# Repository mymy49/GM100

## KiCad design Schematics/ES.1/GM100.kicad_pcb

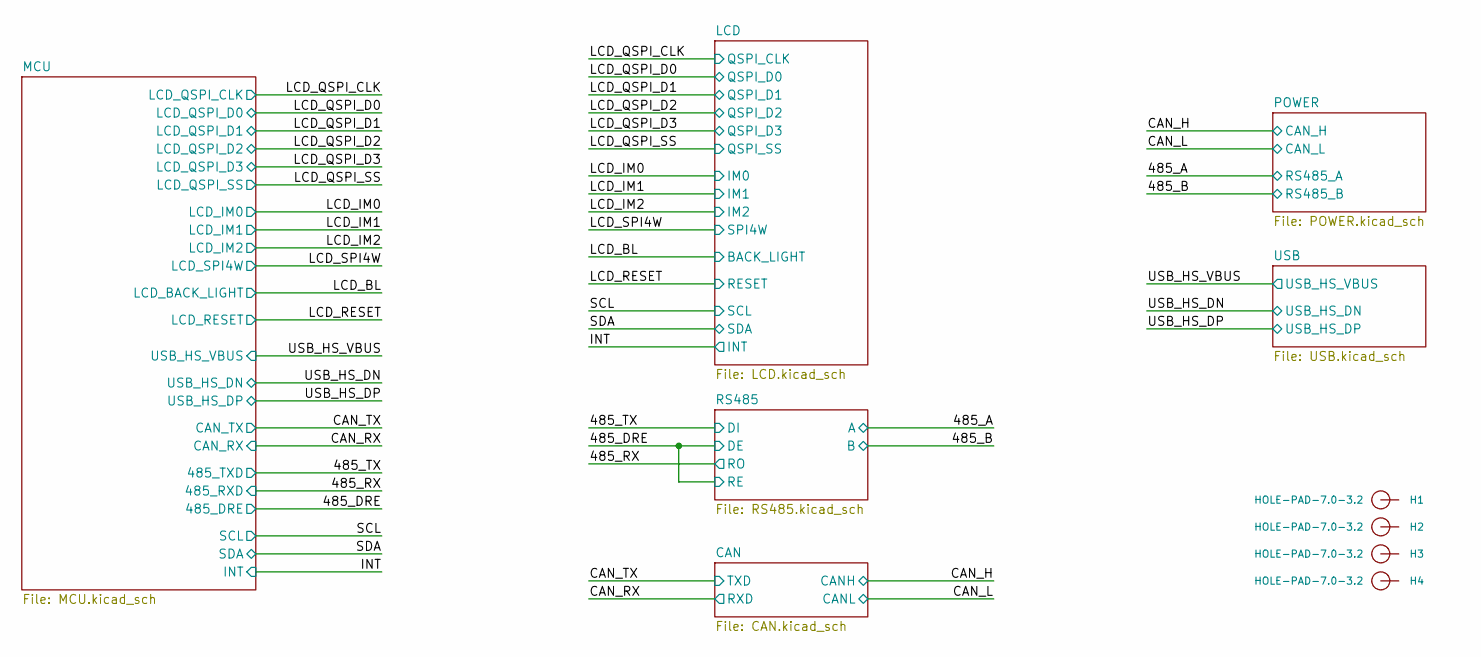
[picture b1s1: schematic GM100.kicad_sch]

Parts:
H1, H2, H3, H4: HOLE-PAD-7.0-3.2; Hole_7_0_3_2

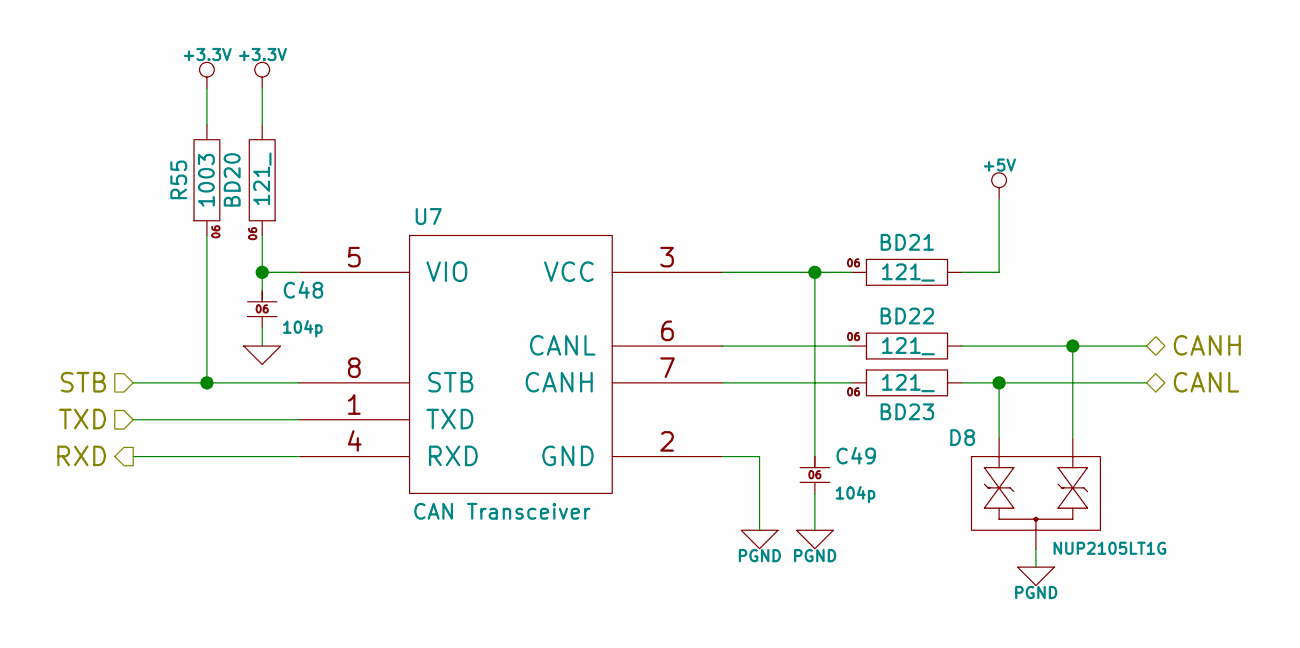
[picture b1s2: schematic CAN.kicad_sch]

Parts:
BD20, BD21, BD22, BD23: BLM18KG121TN1D; 0603; LCSC Part # C85831
C48, C49: 0603B104K500; 0603; LCSC Part # C314282
D8: NUP2105LT1G; SOT23; LCSC Part # C14486
R55: WR06X1003FTL; 0603; LCSC Part # C132374
U7: CA-IF1042LVS-Q1; SOIC-8; LCSC Part # C20598902

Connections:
+3.3V: BD20.2, R55.2; also elsewhere on the board
+5V: BD21.2; also elsewhere on the board
/CAN/STB: R55.1, U7.8 (STB)
/CAN_H: BD22.2, D8.2 (C1); also elsewhere on the board
/CAN_L: BD23.2, D8.1 (A2); also elsewhere on the board
/CAN_RX: U7.4 (RXD); also elsewhere on the board
/CAN_TX: U7.1 (TXD); also elsewhere on the board
GND: C48.1; also elsewhere on the board
unnamed: BD23.1, U7.7 (CANH)
unnamed: BD22.1, U7.6 (CANL)
unnamed: BD21.1, C49.2, U7.3 (VCC)
unnamed: BD20.1, C48.2, U7.5 (VIO)
PGND: C49.1, D8.3 (A1C2), U7.2 (GND); also elsewhere on the board

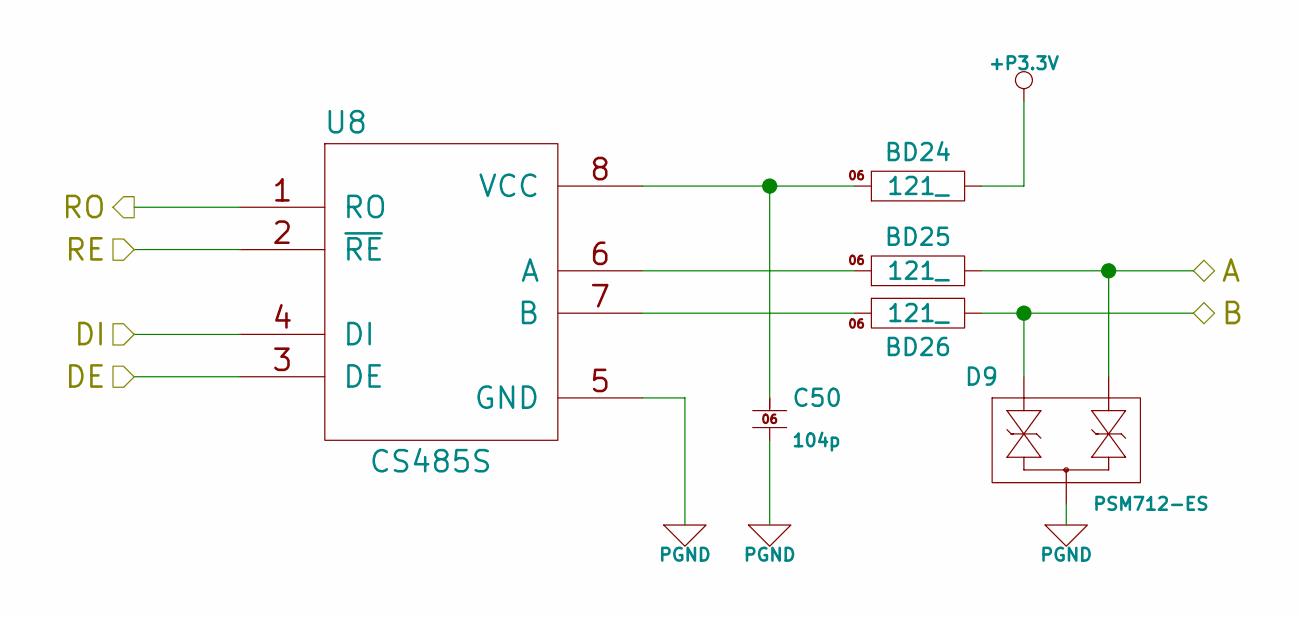
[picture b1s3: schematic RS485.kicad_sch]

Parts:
BD24, BD25, BD26: BLM18KG121TN1D; 0603; LCSC Part # C85831
C50: 0603B104K500; 0603; LCSC Part # C314282
D9: PSM712-ES; SOT23; LCSC Part # C5180294
U8: CS485S; SOIC-8; LCSC Part # C7422593

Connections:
+P3.3V: BD24.2; also elsewhere on the board
/485_A: BD25.2, D9.2 (C1); also elsewhere on the board
/485_B: BD26.2, D9.1 (A2); also elsewhere on the board
/485_DRE: U8.2 (~RE), U8.3 (DE); also elsewhere on the board
/485_RX: U8.1 (RO); also elsewhere on the board
/485_TX: U8.4 (DI); also elsewhere on the board
unnamed: BD25.1, U8.6 (A)
unnamed: BD26.1, U8.7 (B)
unnamed: BD24.1, C50.2, U8.8 (VCC)
PGND: C50.1, D9.3 (A1C2), U8.5 (GND); also elsewhere on the board

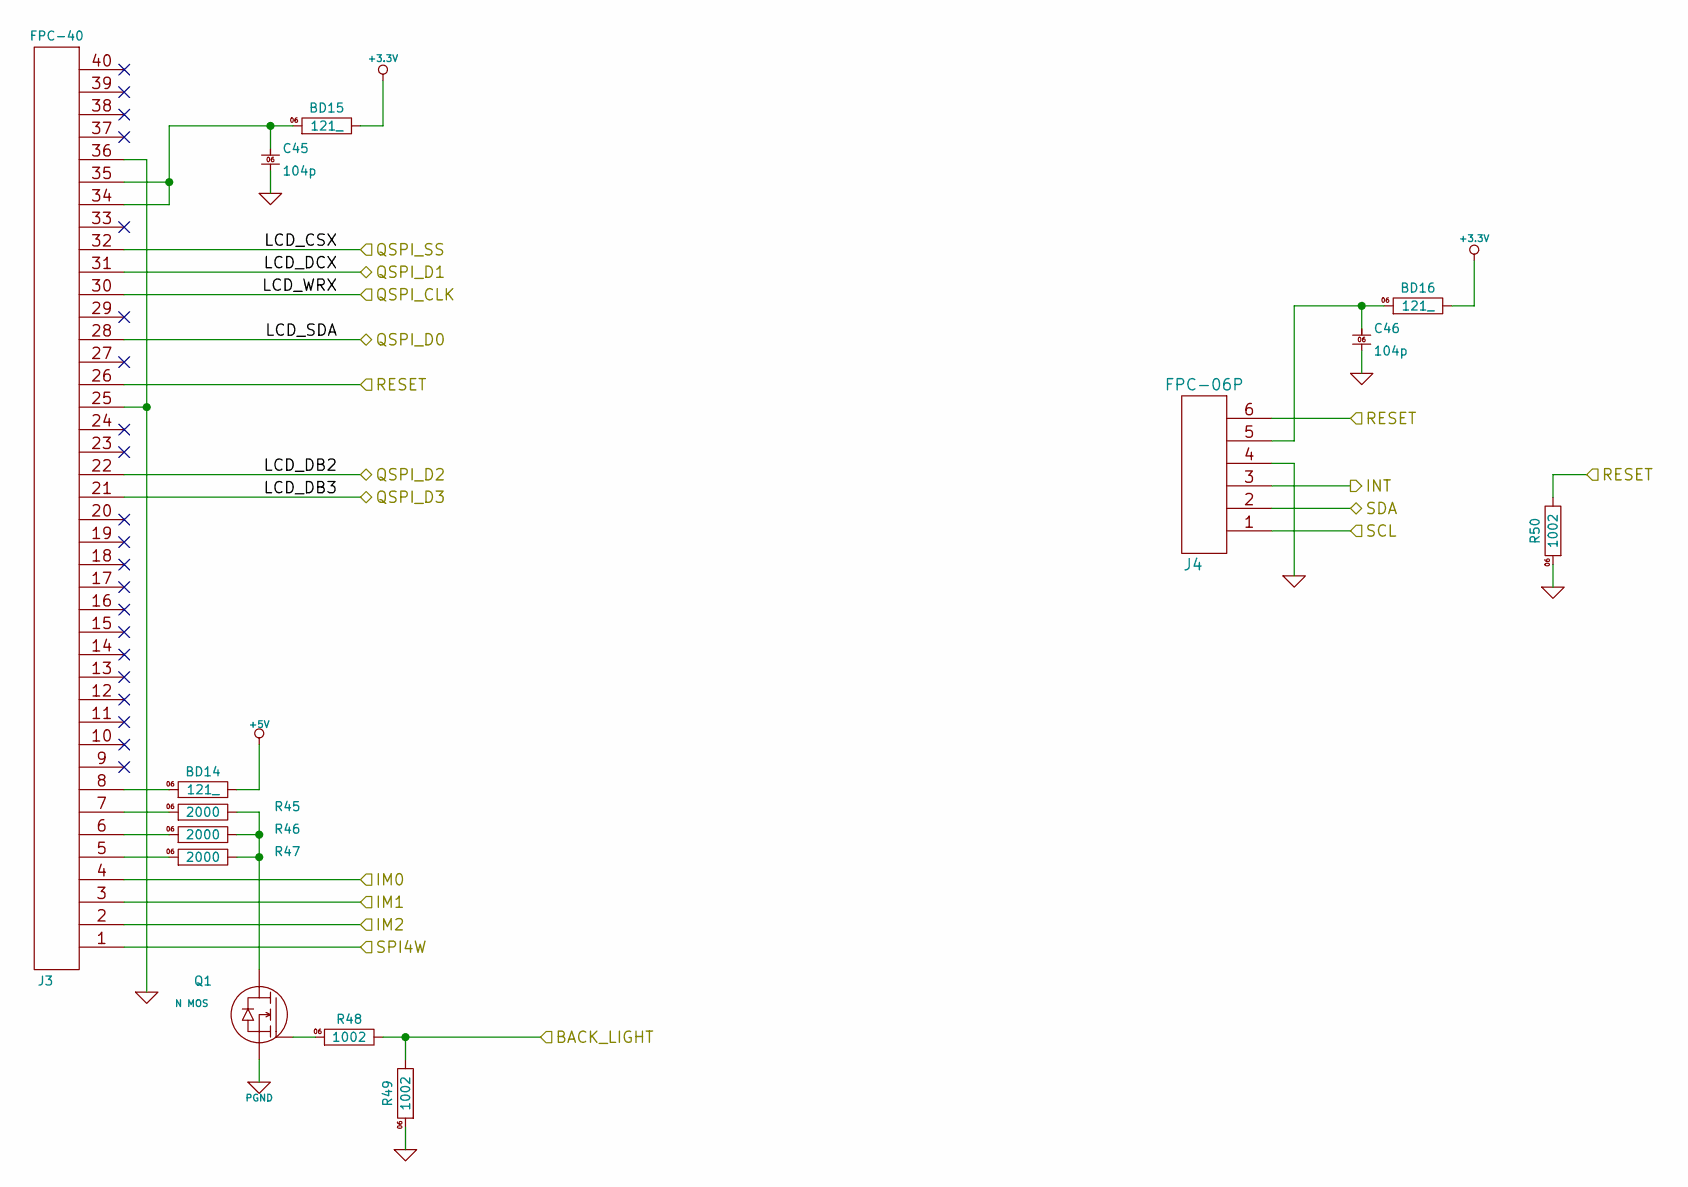
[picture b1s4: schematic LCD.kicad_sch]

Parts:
BD14, BD15, BD16: BLM18KG121TN1D; 0603; LCSC Part # C85831
C45, C46: 0603B104K500; 0603; LCSC Part # C314282
J3: AFC24-S40FIA-00; JUSHUO_AFC24-S40FIA-00; LCSC Part # C262686
J4: AFC24-S06FIA-00; JUSHUO_AFC24-S06FIA-00; LCSC Part # C262679
Q1: 2N7002K-7; SOT23; LCSC Part # C85047
R45, R46, R47: WR06X2000FTL; 0603; LCSC Part # C163878
R48, R49, R50: WR06X1002FTL; 0603; LCSC Part # C108449

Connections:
+3.3V: BD15.2, BD16.2; also elsewhere on the board
+5V: BD14.2; also elsewhere on the board
/INT: J4.3; also elsewhere on the board
/LCD_BL: R48.2, R49.2; also elsewhere on the board
/LCD_IM0: J3.4; also elsewhere on the board
/LCD_IM1: J3.3; also elsewhere on the board
/LCD_IM2: J3.2; also elsewhere on the board
/LCD_QSPI_CLK: J3.30; also elsewhere on the board
/LCD_QSPI_D0: J3.28; also elsewhere on the board
/LCD_QSPI_D1: J3.31; also elsewhere on the board
/LCD_QSPI_D2: J3.22; also elsewhere on the board
/LCD_QSPI_D3: J3.21; also elsewhere on the board
/LCD_QSPI_SS: J3.32; also elsewhere on the board
/LCD_RESET: J3.26, J4.6, R50.2; also elsewhere on the board
/LCD_SPI4W: J3.1; also elsewhere on the board
/SCL: J4.1; also elsewhere on the board
/SDA: J4.2; also elsewhere on the board
GND: C45.1, C46.1, J3.25, J3.36, J4.4, R49.1, R50.1; also elsewhere on the board
unnamed: BD14.1, J3.8
unnamed: BD15.1, C45.2, J3.34, J3.35
unnamed: BD16.1, C46.2, J4.5
unnamed: J3.5, R47.1
unnamed: J3.6, R46.1
unnamed: J3.7, R45.1
unnamed: Q1.3 (D), R45.2, R46.2, R47.2
unnamed: Q1.1 (G), R48.1
PGND: Q1.2 (S); also elsewhere on the board

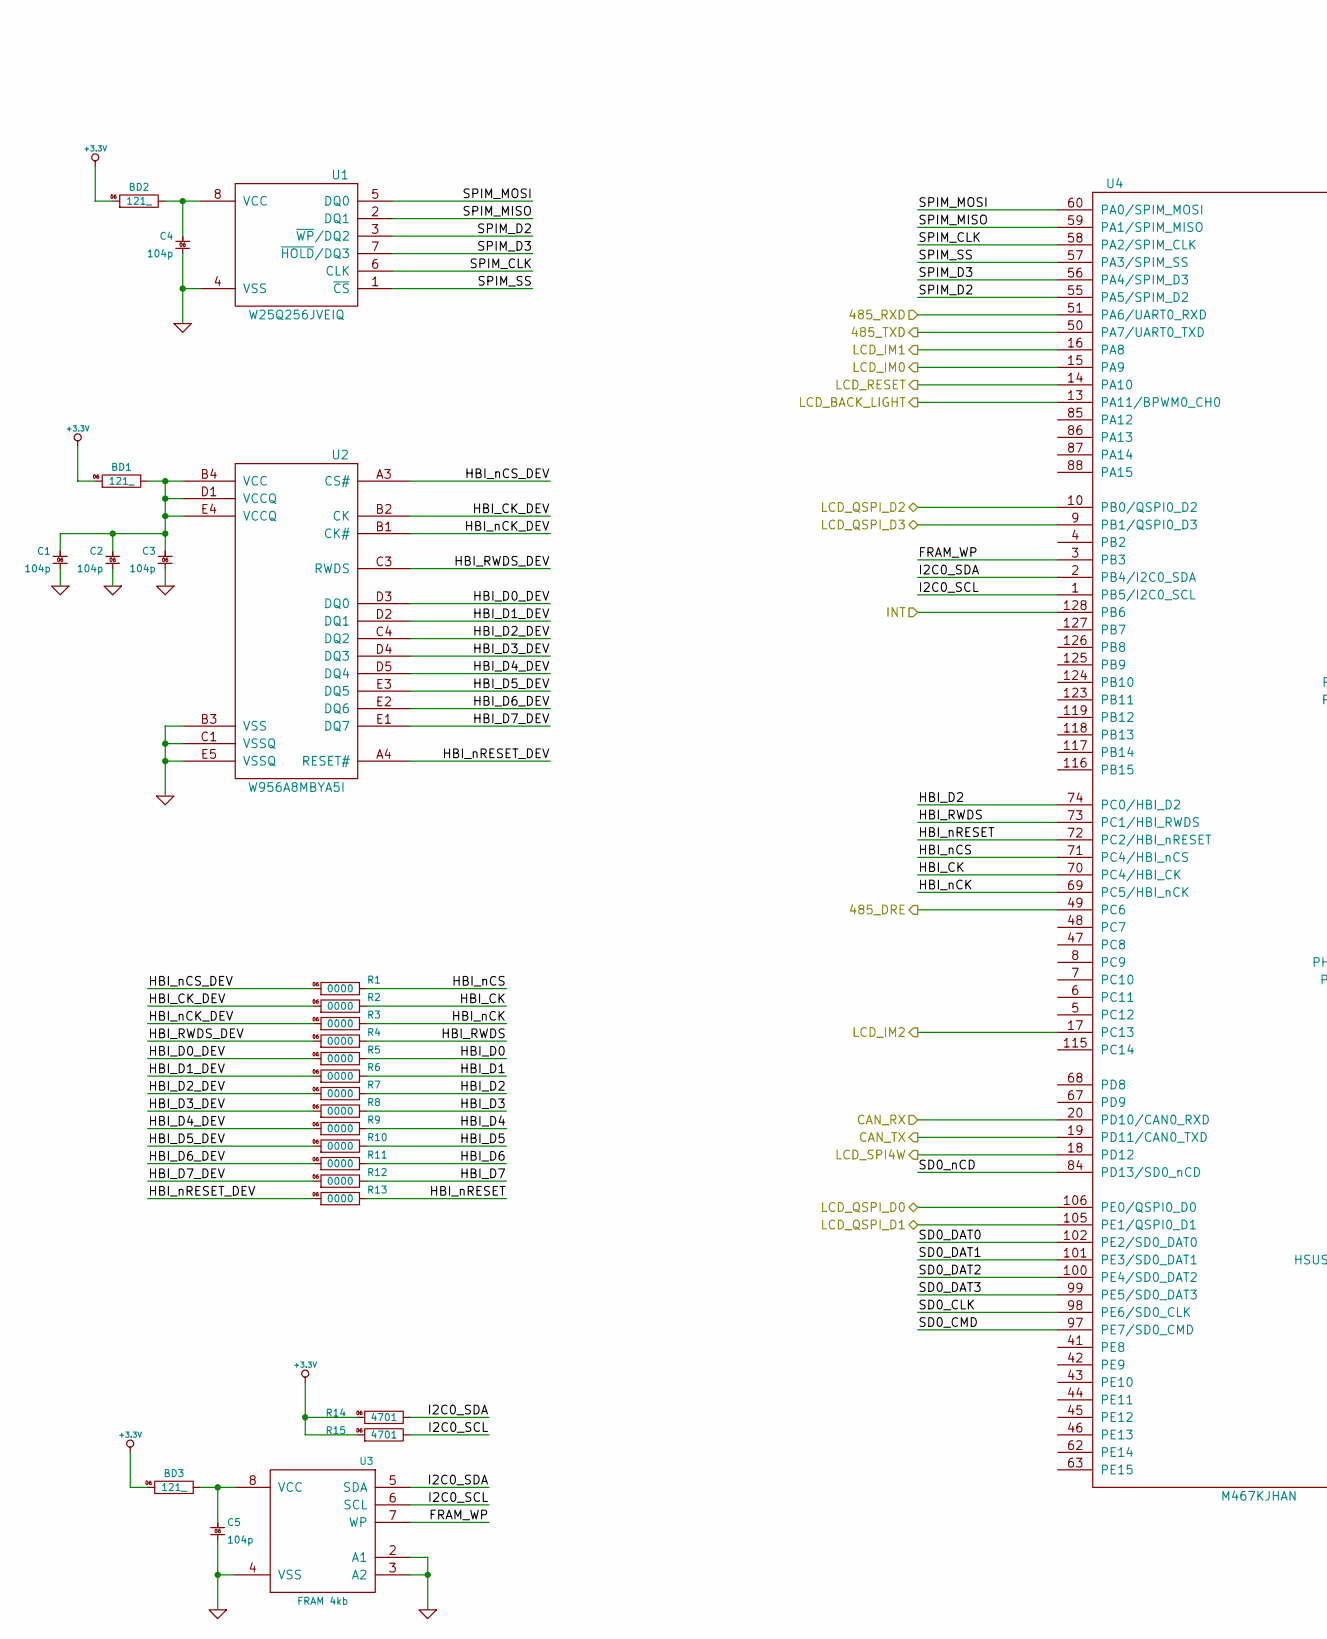
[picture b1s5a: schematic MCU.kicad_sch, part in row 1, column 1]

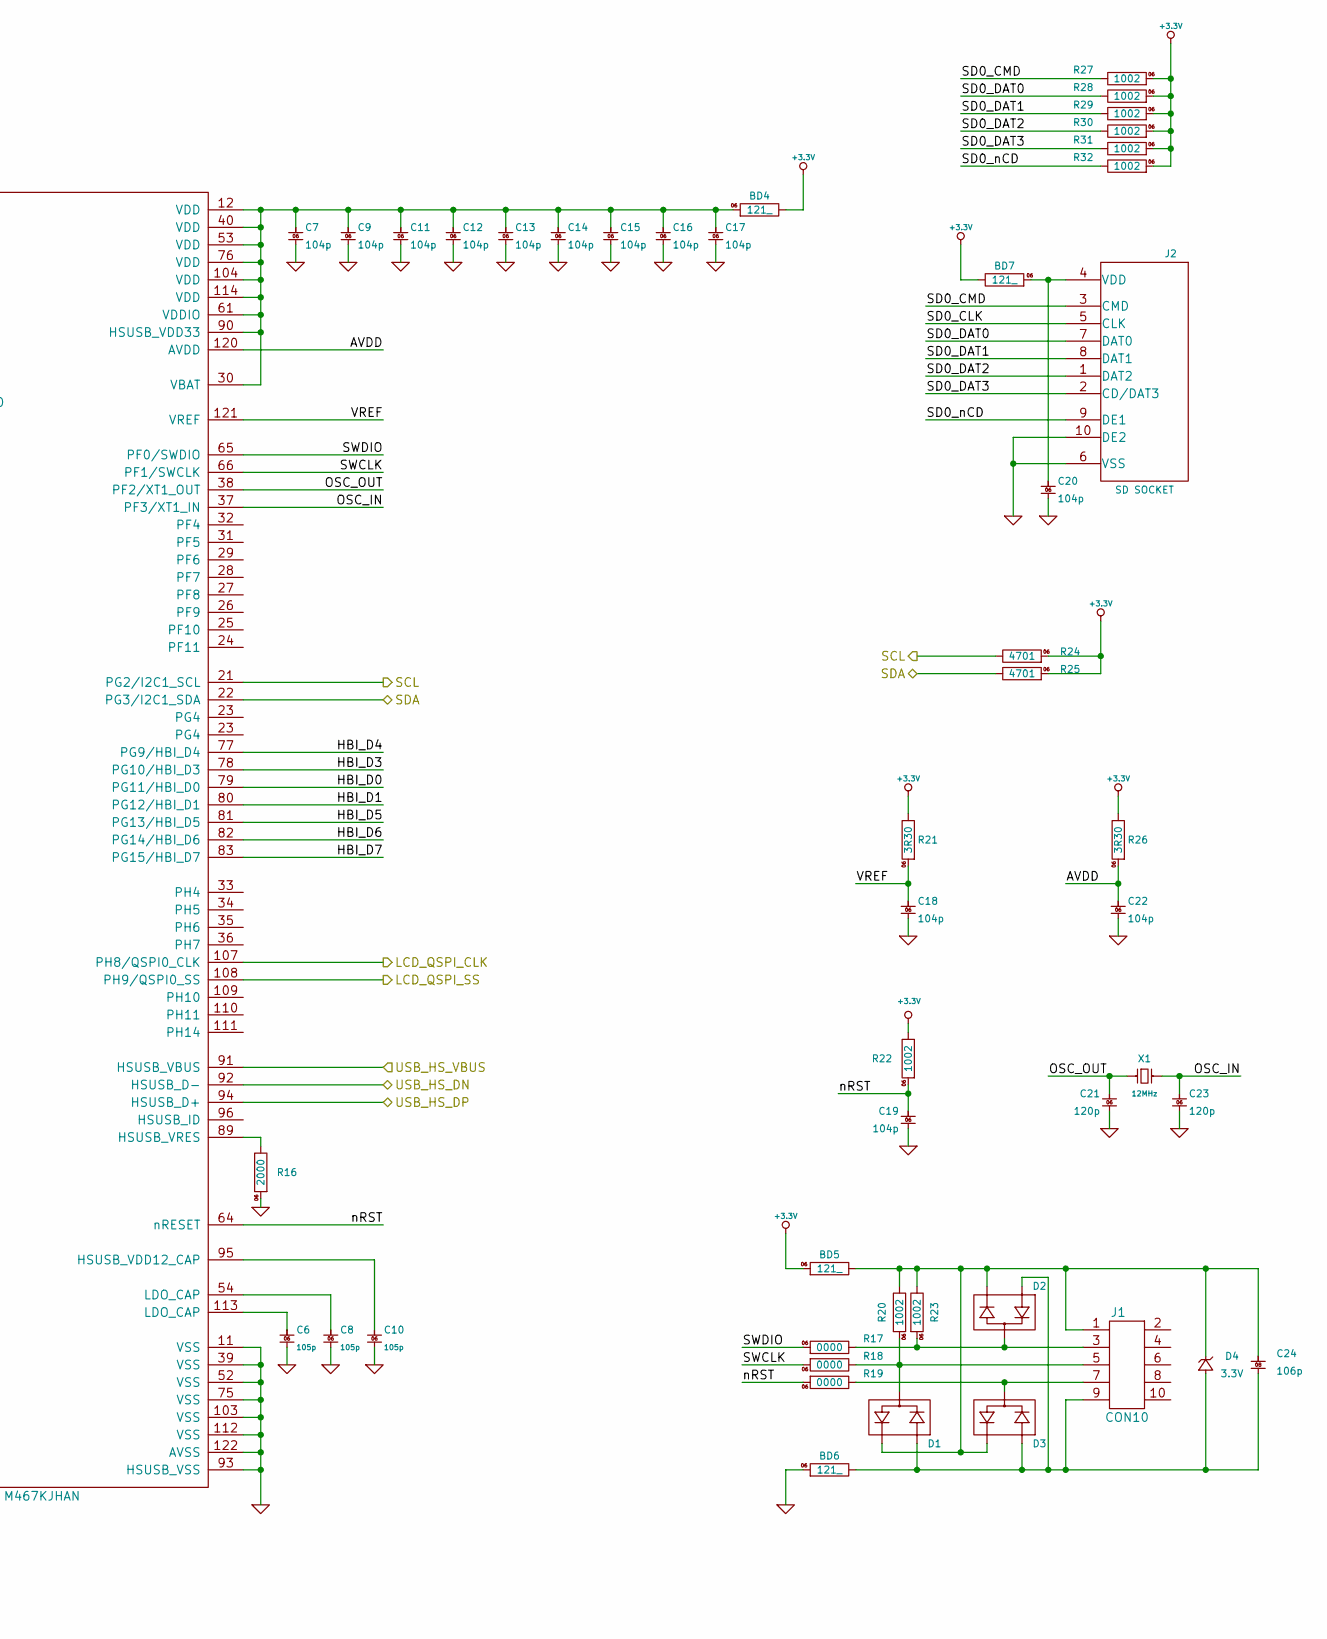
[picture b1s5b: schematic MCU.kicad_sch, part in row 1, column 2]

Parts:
BD1, BD2, BD3, BD4, BD5, BD6, BD7: BLM18KG121TN1D; 0603; LCSC Part # C85831
C1, C2, C3, C4, C5, C7, C9, C11, C12, C13, C14, C15, C16, C17, C18, C19, C20, C22: 0603B104K500; 0603; LCSC Part # C314282
C6, C8, C10: 0603B105K250; 0603; LCSC Part # C388002
C21, C23: 0603N120J500; 0603; LCSC Part # C123529
C24: 0805X106K100; 0805; LCSC Part # C105505
D1, D2, D3: KDS226; SOT23; LCSC Part # C73208
D4: ESD5Z3.3T1G-MS; SOD523; LCSC Part # C3008119
J1: HC-JN254-2-05-W; HCTL_HC-JN254-2-05-W; LCSC Part # C5372873
J2: SD-01A; LCSC Part # C693845
R1, R2, R3, R4, R5, R6, R7, R8, R9, R10, R11, R12, R13, R17, R18, R19: WR06X0000JTL; 0603; LCSC Part # C163836
R14, R15, R24, R25: WR06X4701FTL; 0603; LCSC Part # C163914
R16: WR06X2000FTL; 0603; LCSC Part # C163878
R20, R22, R23, R27, R28, R29, R30, R31, R32: WR06X1002FTL; 0603; LCSC Part # C108449
R21, R26: WR06W3R30FTL; 0603; LCSC Part # C168319
U1: W25Q256JVEIQ; 8-WSON_8x6; LCSC Part # C97522
U2: W956A8MBYA5I; TFBGA24_6x8mm_P1.00mm; LCSC Part # C5375118
U3: FM24CL04B-G; SOIC-8; LCSC Part # C914924
U4: M467KJHAN; LQFP-128_14x14mm_P0.4mm
X1: CF4012M00020; CRSTAL_SMD_3225-4Pin; LCSC Part # C5916243

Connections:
+3.3V: BD1.1, BD2.1, BD3.1, BD4.2, BD5.1, BD7.2, R14.1, R15.1, R21.2, R22.2, R24.1, R25.1, R26.2, R27.1, R28.1, R29.1, R30.1, R31.1, R32.1; also elsewhere on the board
/485_DRE: U4.49 (PC6); also elsewhere on the board
/485_RX: U4.51 (PA6/UART0_RXD); also elsewhere on the board
/485_TX: U4.50 (PA7/UART0_TXD); also elsewhere on the board
/CAN_RX: U4.20 (PD10/CAN0_RXD); also elsewhere on the board
/CAN_TX: U4.19 (PD11/CAN0_TXD); also elsewhere on the board
/INT: U4.128 (PB6); also elsewhere on the board
/LCD_BL: U4.13 (PA11/BPWM0_CH0); also elsewhere on the board
/LCD_IM0: U4.15 (PA9); also elsewhere on the board
/LCD_IM1: U4.16 (PA8); also elsewhere on the board
/LCD_IM2: U4.17 (PC13); also elsewhere on the board
/LCD_QSPI_CLK: U4.107 (PH8/QSPI0_CLK); also elsewhere on the board
/LCD_QSPI_D0: U4.106 (PE0/QSPI0_D0); also elsewhere on the board
/LCD_QSPI_D1: U4.105 (PE1/QSPI0_D1); also elsewhere on the board
/LCD_QSPI_D2: U4.10 (PB0/QSPI0_D2); also elsewhere on the board
/LCD_QSPI_D3: U4.9 (PB1/QSPI0_D3); also elsewhere on the board
/LCD_QSPI_SS: U4.108 (PH9/QSPI0_SS); also elsewhere on the board
/LCD_RESET: U4.14 (PA10); also elsewhere on the board
/LCD_SPI4W: U4.18 (PD12); also elsewhere on the board
/MCU/AVDD: C22.2, R26.1, U4.120 (AVDD)
/MCU/FRAM_WP: U3.7 (WP), U4.3 (PB3)
/MCU/HBI_CK: R2.2, U4.70 (PC4/HBI_CK)
/MCU/HBI_CK_DEV: R2.1, U2.B2 (CK)
/MCU/HBI_D0: R5.2, U4.79 (PG11/HBI_D0)
/MCU/HBI_D0_DEV: R5.1, U2.D3 (DQ0)
/MCU/HBI_D1: R6.2, U4.80 (PG12/HBI_D1)
/MCU/HBI_D1_DEV: R6.1, U2.D2 (DQ1)
/MCU/HBI_D2: R7.2, U4.74 (PC0/HBI_D2)
/MCU/HBI_D2_DEV: R7.1, U2.C4 (DQ2)
/MCU/HBI_D3: R8.2, U4.78 (PG10/HBI_D3)
/MCU/HBI_D3_DEV: R8.1, U2.D4 (DQ3)
/MCU/HBI_D4: R9.2, U4.77 (PG9/HBI_D4)
/MCU/HBI_D4_DEV: R9.1, U2.D5 (DQ4)
/MCU/HBI_D5: R10.2, U4.81 (PG13/HBI_D5)
/MCU/HBI_D5_DEV: R10.1, U2.E3 (DQ5)
/MCU/HBI_D6: R11.2, U4.82 (PG14/HBI_D6)
/MCU/HBI_D6_DEV: R11.1, U2.E2 (DQ6)
/MCU/HBI_D7: R12.2, U4.83 (PG15/HBI_D7)
/MCU/HBI_D7_DEV: R12.1, U2.E1 (DQ7)
/MCU/HBI_RWDS: R4.2, U4.73 (PC1/HBI_RWDS)
/MCU/HBI_RWDS_DEV: R4.1, U2.C3 (RWDS)
/MCU/HBI_nCK: R3.2, U4.69 (PC5/HBI_nCK)
/MCU/HBI_nCK_DEV: R3.1, U2.B1 (CK#)
/MCU/HBI_nCS: R1.2, U4.71 (PC4/HBI_nCS)
/MCU/HBI_nCS_DEV: R1.1, U2.A3 (CS#)
/MCU/HBI_nRESET: R13.2, U4.72 (PC2/HBI_nRESET)
/MCU/HBI_nRESET_DEV: R13.1, U2.A4 (RESET#)
/MCU/I2C0_SCL: R15.2, U3.6 (SCL), U4.1 (PB5/I2C0_SCL)
/MCU/I2C0_SDA: R14.2, U3.5 (SDA), U4.2 (PB4/I2C0_SDA)
/MCU/OSC_IN: C23.2, U4.37 (PF3/XT1_IN), X1.3
/MCU/OSC_OUT: C21.2, U4.38 (PF2/XT1_OUT), X1.1
/MCU/SD0_CLK: J2.5 (CLK), U4.98 (PE6/SD0_CLK)
/MCU/SD0_CMD: J2.3 (CMD), R27.2, U4.97 (PE7/SD0_CMD)
/MCU/SD0_DAT0: J2.7 (DAT0), R28.2, U4.102 (PE2/SD0_DAT0)
/MCU/SD0_DAT1: J2.8 (DAT1), R29.2, U4.101 (PE3/SD0_DAT1)
/MCU/SD0_DAT2: J2.1 (DAT2), R30.2, U4.100 (PE4/SD0_DAT2)
/MCU/SD0_DAT3: J2.2 (CD/DAT3), R31.2, U4.99 (PE5/SD0_DAT3)
/MCU/SD0_nCD: J2.9 (DE1), R32.2, U4.84 (PD13/SD0_nCD)
/MCU/SPIM_CLK: U1.6 (CLK), U4.58 (PA2/SPIM_CLK)
/MCU/SPIM_D2: U1.3 (~WP/DQ2), U4.55 (PA5/SPIM_D2)
/MCU/SPIM_D3: U1.7 (~HOLD/DQ3), U4.56 (PA4/SPIM_D3)
/MCU/SPIM_MISO: U1.2 (DQ1), U4.59 (PA1/SPIM_MISO)
/MCU/SPIM_MOSI: U1.5 (DQ0), U4.60 (PA0/SPIM_MOSI)
/MCU/SPIM_SS: U1.1 (~CS), U4.57 (PA3/SPIM_SS)
/MCU/SWCLK: R18.1, U4.66 (PF1/SWCLK)
/MCU/SWDIO: R17.1, U4.65 (PF0/SWDIO)
/MCU/VREF: C18.2, R21.1, U4.121 (VREF)
/MCU/nRST: C19.2, R19.1, R22.1, U4.64 (nRESET)
/SCL: R24.2, U4.21 (PG2/I2C1_SCL); also elsewhere on the board
/SDA: R25.2, U4.22 (PG3/I2C1_SDA); also elsewhere on the board
/USB_HS_DN: U4.92 (HSUSB_D-); also elsewhere on the board
/USB_HS_DP: U4.94 (HSUSB_D+); also elsewhere on the board
/USB_HS_VBUS: U4.91 (HSUSB_VBUS); also elsewhere on the board
GND: BD6.1, C1.1, C2.1, C3.1, C4.1, C5.1, C6.1, C7.1, C8.1, C9.1, C10.1, C11.1, C12.1, C13.1, C14.1, C15.1, C16.1, C17.1, C18.1, C19.1, C20.1, C21.1, C22.1, C23.1, J2.6 (VSS), J2.10 (DE2), R16.1, U1.4 (VSS), U2.B3 (VSS), U2.C1 (VSSQ), U2.E5 (VSSQ), U3.2 (A1), U3.3 (A2), U3.4 (VSS), U4.11 (VSS), U4.39 (VSS), U4.52 (VSS), U4.75 (VSS), U4.93 (HSUSB_VSS), U4.103 (VSS), U4.112 (VSS), U4.122 (AVSS); also elsewhere on the board
unnamed: C6.2, U4.113 (LDO_CAP)
unnamed: C8.2, U4.54 (LDO_CAP)
unnamed: D1.3 (A1C2), J1.5, R18.2, R20.1
unnamed: BD6.2, C24.1, D1.1 (A2), D2.1 (A2), D3.1 (A2), D4.1 (A), J1.9
unnamed: BD5.2, C24.2, D1.2 (C1), D2.2 (C1), D3.2 (C1), D4.2 (K), J1.1, R20.2, R23.2
unnamed: D2.3 (A1C2), J1.3, R17.2, R23.1
unnamed: D3.3 (A1C2), J1.7, R19.2
unnamed: BD7.1, C20.2, J2.4 (VDD)
unnamed: BD2.2, C4.2, U1.8 (VCC)
unnamed: BD1.2, C1.2, C2.2, C3.2, U2.B4 (VCC), U2.D1 (VCCQ), U2.E4 (VCCQ)
unnamed: BD3.2, C5.2, U3.8 (VCC)
unnamed: C10.2, U4.95 (HSUSB_VDD12_CAP)
unnamed: BD4.1, C7.2, C9.2, C11.2, C12.2, C13.2, C14.2, C15.2, C16.2, C17.2, U4.12 (VDD), U4.30 (VBAT), U4.40 (VDD), U4.53 (VDD), U4.61 (VDDIO), U4.76 (VDD), U4.90 (HSUSB_VDD33), U4.104 (VDD), U4.114 (VDD)
unnamed: R16.2, U4.89 (HSUSB_VRES)

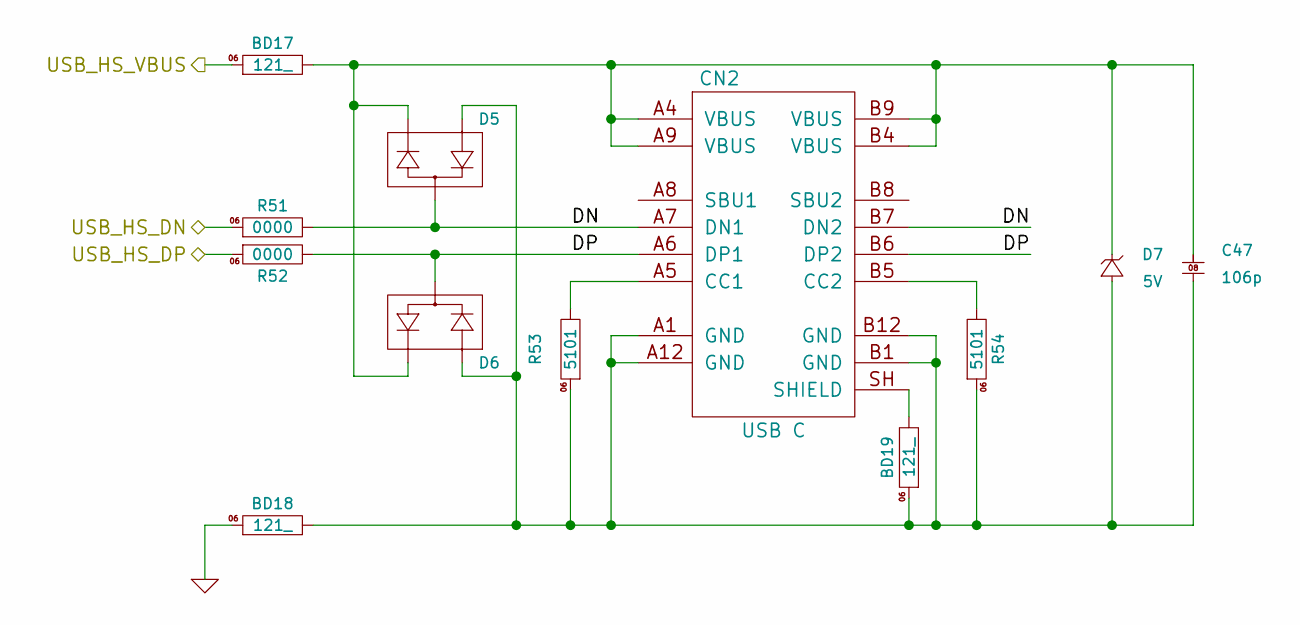
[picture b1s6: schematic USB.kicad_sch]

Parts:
BD17, BD18, BD19: BLM18KG121TN1D; 0603; LCSC Part # C85831
C47: 0805X106K100; 0805; LCSC Part # C105505
CN2: GT-USB-7010ASV; LCSC Part # C2988369
D5, D6: KDS226; SOT23; LCSC Part # C73208
D7: SJD12A05L01; SOD123; LCSC Part # C5563731
R51, R52: WR06X0000JTL; 0603; LCSC Part # C163836
R53, R54: WR06X5101FTL; 0603; LCSC Part # C113390

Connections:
/USB/DN: CN2.A7 (DN1), CN2.B7 (DN2), D5.3 (A1C2), R51.2
/USB/DP: CN2.A6 (DP1), CN2.B6 (DP2), D6.3 (A1C2), R52.2
/USB_HS_DN: R51.1; also elsewhere on the board
/USB_HS_DP: R52.1; also elsewhere on the board
/USB_HS_VBUS: BD17.1; also elsewhere on the board
GND: BD18.1; also elsewhere on the board
unnamed: CN2.A5 (CC1), R53.2
unnamed: CN2.B5 (CC2), R54.2
unnamed: BD19.2, CN2.SH (SHIELD)
unnamed: BD18.2, BD19.1, C47.1, CN2.A1 (GND), CN2.A12 (GND), CN2.B1 (GND), CN2.B12 (GND), D5.1 (A2), D6.1 (A2), D7.1 (A), R53.1, R54.1
unnamed: BD17.2, C47.2, CN2.A4 (VBUS), CN2.A9 (VBUS), CN2.B4 (VBUS), CN2.B9 (VBUS), D5.2 (C1), D6.2 (C1), D7.2 (K)

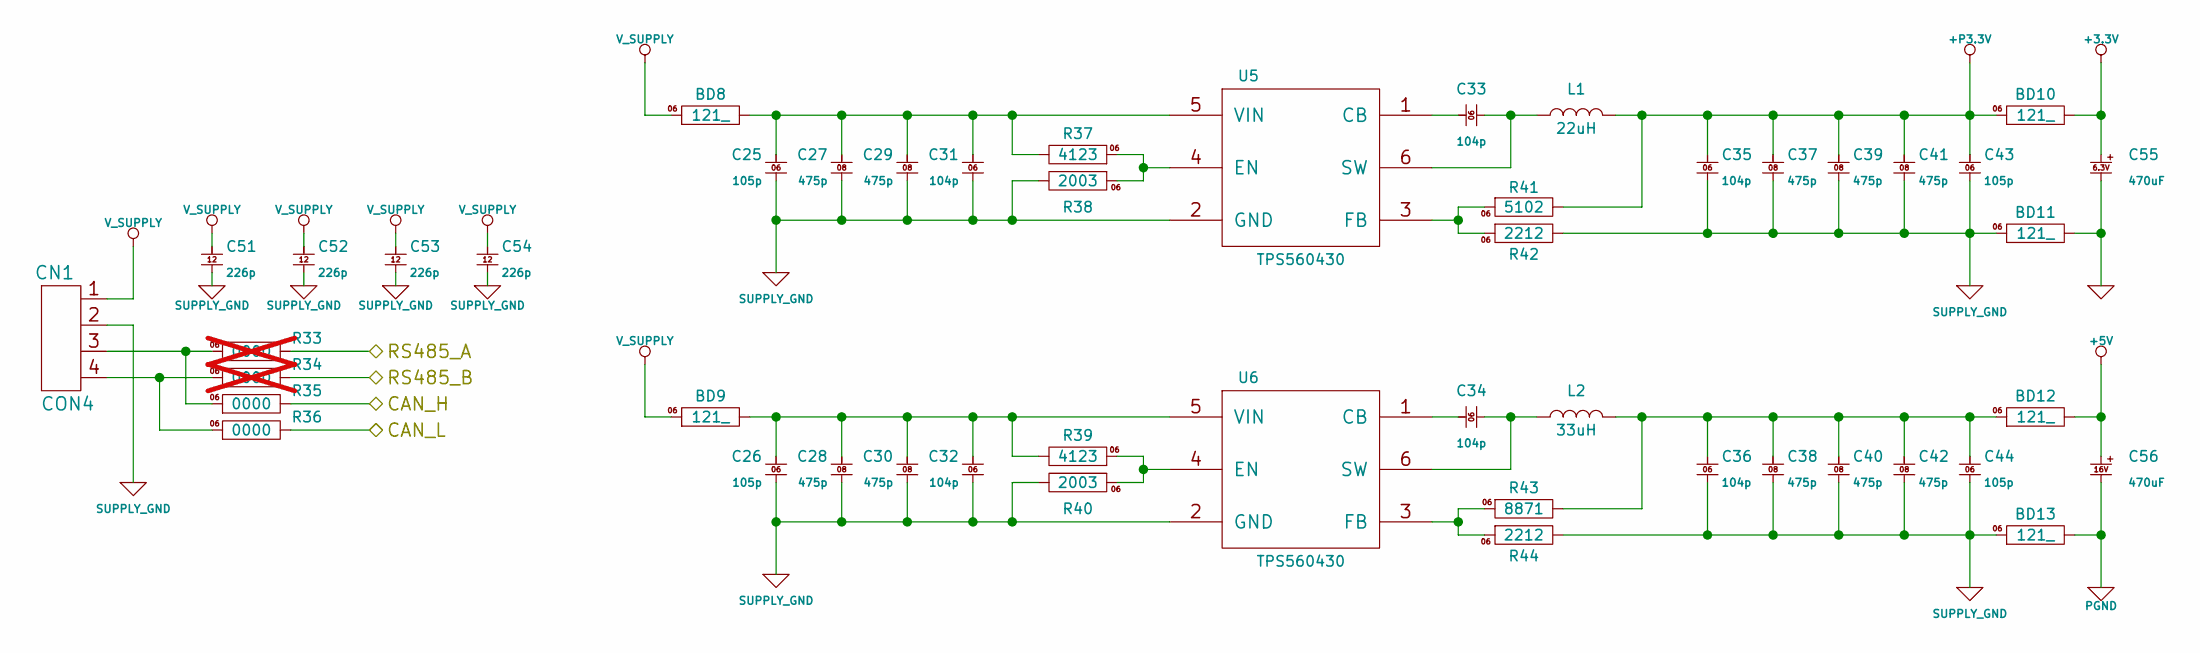
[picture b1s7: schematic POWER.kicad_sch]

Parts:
BD8, BD9, BD10, BD11, BD12, BD13: BLM18KG121TN1D; 0603; LCSC Part # C85831
C25, C26, C43, C44: 0603B105K250; 0603; LCSC Part # C388002
C27, C28, C29, C30, C37, C38, C39, C40, C41, C42: 0805B475K160; 0805; LCSC Part # C123624
C31, C32, C33, C34, C35, C36: 0603B104K500; 0603; LCSC Part # C314282
C51, C52, C53, C54: 1206B226K100; 1206; LCSC Part # C237195
C55: RVT0J471M0607; CP_Elec_6.3x7.7; LCSC Part # C3354
C56: VEJ471M1CTR-0810; CP_Elec_8x10; LCSC Part # C176671
CN1: WJ2EDGRC-5.08-4P; KANGNEX_WJ2EDGRC-5.08-4P; LCSC Part # C8446
L1: XRNR4030-22uH/M; XR_XRNR4030; LCSC Part # C5289362
L2: XRNR4030-33uH/M; XR_XRNR4030; LCSC Part # C5289365
R33, R34: WR06X0000JTL; 0603; LCSC Part # C163836; not fitted
R35, R36: WR06X0000JTL; 0603; LCSC Part # C163836
R37, R39: WR06X4123FTL; 0603; LCSC Part # C170594
R38, R40: WR06X2003FTL; 0603; LCSC Part # C163877
R41: WR06X5102FTL; 0603; LCSC Part # C163933
R42, R44: WR06X2212FTL; 0603; LCSC Part # C168292
R43: WR06X8871FTL; 0603; LCSC Part # C170687
U5, U6: TPS560430XDBV; DBV0006A; LCSC Part # C524782

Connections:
+3.3V: BD10.2, C55.1; also elsewhere on the board
+5V: BD12.2, C56.1; also elsewhere on the board
+P3.3V: BD10.1, C35.2, C37.2, C39.2, C41.2, C43.2, L1.2, R41.2; also elsewhere on the board
/485_A: R33.2; also elsewhere on the board
/485_B: R34.2; also elsewhere on the board
/CAN_H: R35.2; also elsewhere on the board
/CAN_L: R36.2; also elsewhere on the board
GND: BD11.2, C55.2; also elsewhere on the board
unnamed: BD12.1, C36.2, C38.2, C40.2, C42.2, C44.2, L2.2, R43.2
unnamed: CN1.3, R33.1, R35.1
unnamed: CN1.4, R34.1, R36.1
unnamed: C33.2, U5.1 (CB)
unnamed: R37.1, R38.1, U5.4 (EN)
unnamed: R41.1, R42.1, U5.3 (FB)
unnamed: C33.1, L1.1, U5.6 (SW)
unnamed: BD8.2, C25.2, C27.2, C29.2, C31.2, R37.2, U5.5 (VIN)
unnamed: C34.2, U6.1 (CB)
unnamed: R39.1, R40.1, U6.4 (EN)
unnamed: R43.1, R44.1, U6.3 (FB)
unnamed: C34.1, L2.1, U6.6 (SW)
unnamed: BD9.2, C26.2, C28.2, C30.2, C32.2, R39.2, U6.5 (VIN)
PGND: BD13.2, C56.2; also elsewhere on the board
SUPPLY_GND: BD11.1, BD13.1, C25.1, C26.1, C27.1, C28.1, C29.1, C30.1, C31.1, C32.1, C35.1, C36.1, C37.1, C38.1, C39.1, C40.1, C41.1, C42.1, C43.1, C44.1, C51.1, C52.1, C53.1, C54.1, CN1.2, R38.2, R40.2, R42.2, R44.2, U5.2 (GND), U6.2 (GND)
V_SUPPLY: BD8.1, BD9.1, C51.2, C52.2, C53.2, C54.2, CN1.1

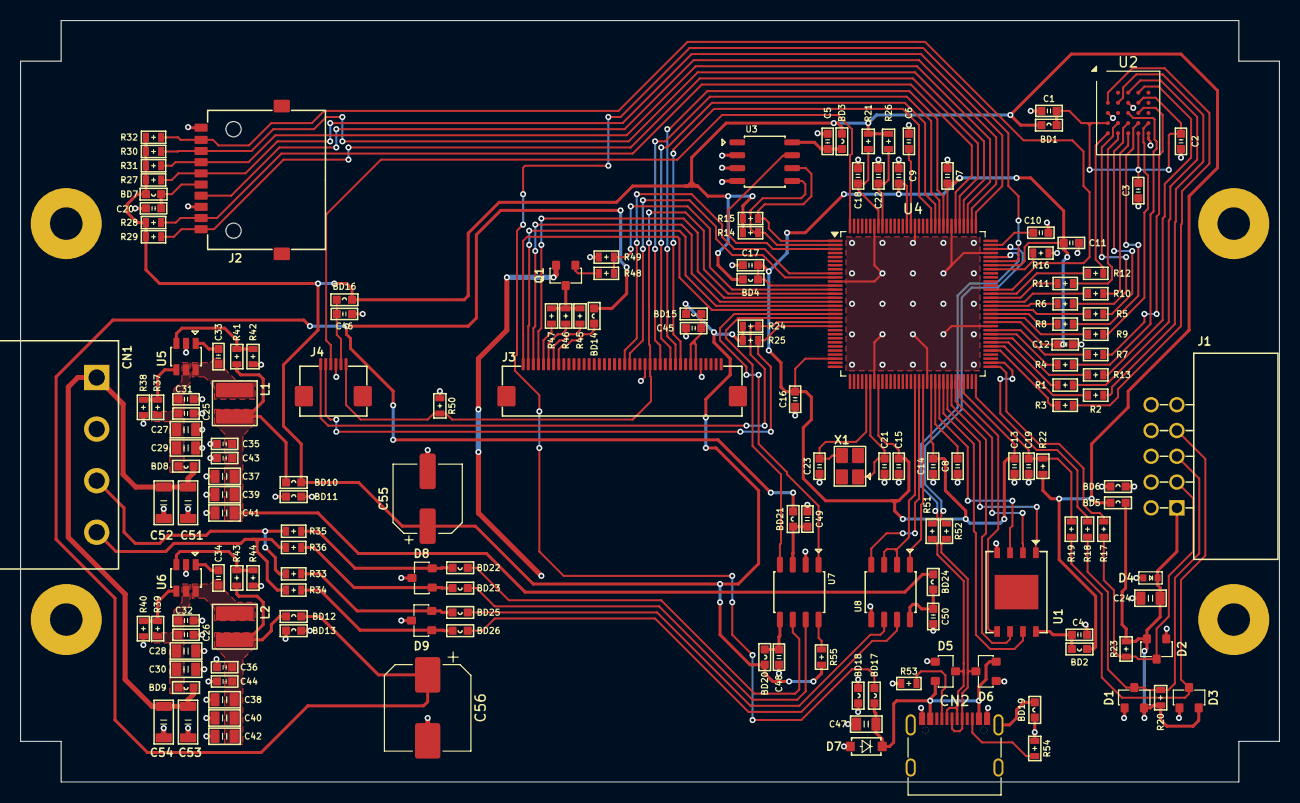
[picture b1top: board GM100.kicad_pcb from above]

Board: 2 copper layers, 123.9 x 74.9 mm, 168 parts (0 on the bottom side), 133 nets.

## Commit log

2026-05-09 - Add ES.1 circuit
2026-05-09 - Add yss OS submodule
2026-05-09 - Create an empty example project
2026-05-09 - Fixed an issue with incorrect file paths in peripheral device registers.
2026-05-09 Add code to initialize default peripherals
2026-05-09 - Add FM24CL04B submodule
2026-05-09 - Add FM24CL04B initialization code
2026-05-10 - Add TurtleShip GUI submodule
2026-05-10 Revert "- Add TurtleShip GUI submodule"
    This reverts commit 4d85d0f64f6f4265e2bb546210eac511a86cb74c.
2026-05-10 - Add P4309N_DCT submodule
2026-05-10 - The functionality of the P4309N_DCT module has not been verified, but code at a level that does not cause errors has been registered.
2026-05-10 - LCD color clearing function test completed
2026-05-10 - Changed to use DMA for TFT-LCD screen refresh
2026-05-17 - Add GT911 touchscreen initialization code
2026-05-17 - Added initialization code for HyperRAM (W956A8MBYA5I)
2026-05-17 - Writing BSP Code
2026-05-17 Change source code path
2026-05-23 The "example_line_drawing" example project has been added.
2026-05-23 Operating System updated
